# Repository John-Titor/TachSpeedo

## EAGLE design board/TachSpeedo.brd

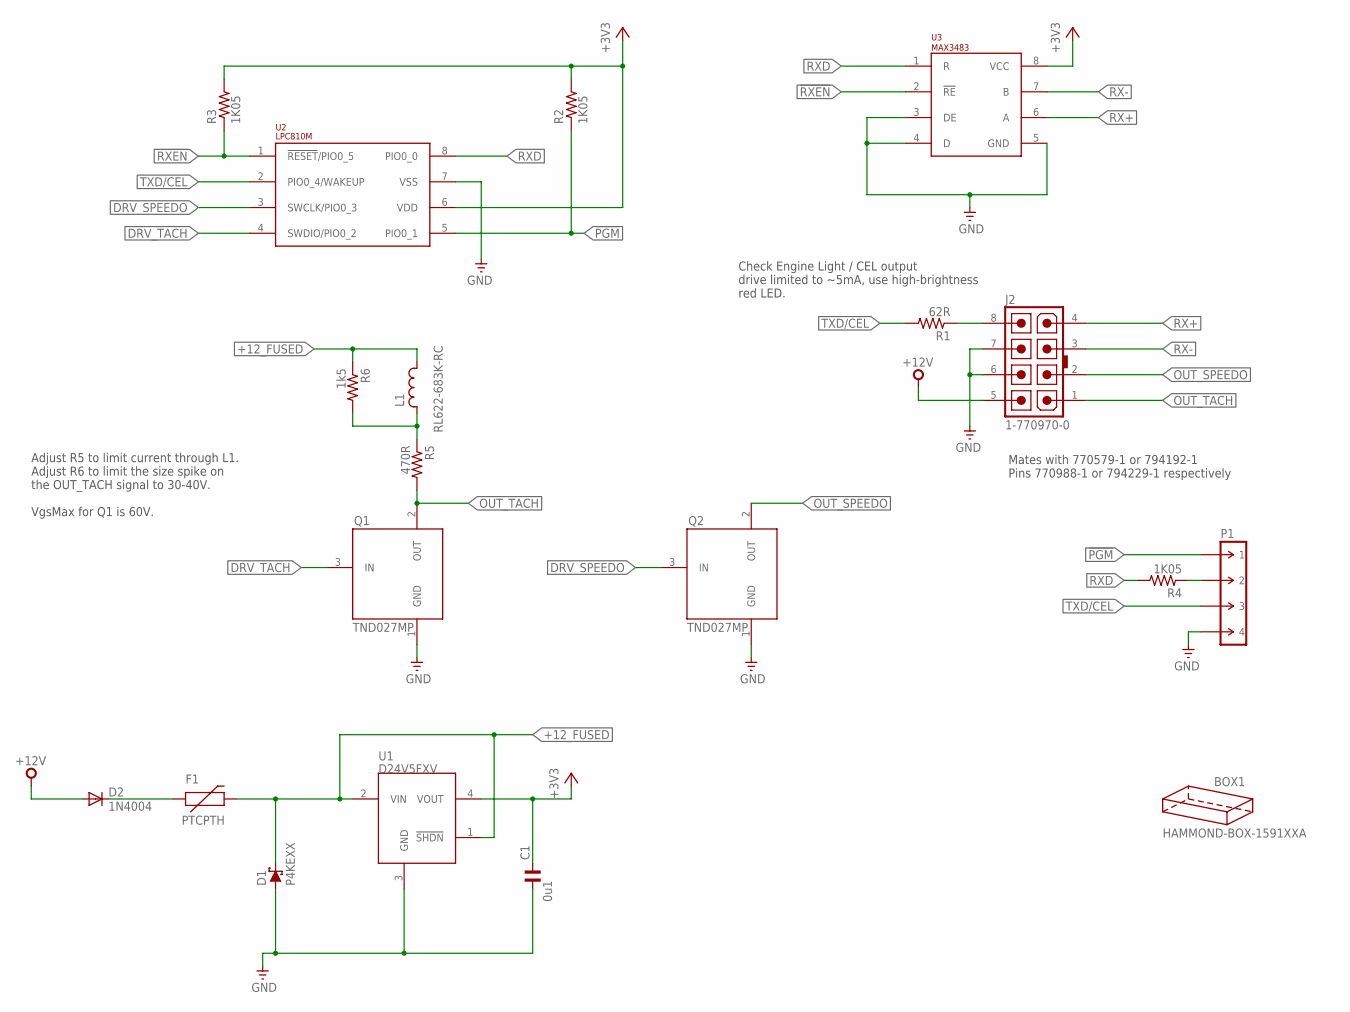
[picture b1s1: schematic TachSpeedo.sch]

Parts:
BOX1: HAMMOND-BOX-1591XXA; 1591XXA; PARTNO 1591XXAFLBK
C1: 0u1; C025-024X044; PARTNO FK18X7R1E104K
D1: P4KEXX; DO41-10; PARTNO P4KE30CA
D2: 1N4004; DO41-10; PARTNO 1N4004
F1: PTCPTH; PTC; PARTNO 600R150-RBZR
J2: 1-770970-0; PARTNO 1-770970-0
L1: RL622-683K-RC; RL622; PARTNO RL622-563K-RC
P1: M-1X04-SIP-100-40; SIP-100-04-40; PARTNO 961104-6404-AR
Q1, Q2: TND027MP; TO-92; PARTNO TND027MP-AZ
R1: 62R; 0207/10; PARTNO MFR-25FTE52-62R
R2, R3, R4: 1K05; 0207/10; PARTNO MFR-25FBF52-1K05
R5: 470R; 0207/10; PARTNO MFR-25FBF52-470R
R6: 1k5; 0207/10; PARTNO MFR-25FRF52-1K5
U1: D24V5FXV; SIP-100-04-40
U2: LPC810M; DIL08; PARTNO LPC810M021FN8FP
U3: MAX3483; DIL08; PARTNO MAX3483CPA+

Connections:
!PGM: P1.1, R2.1, U2.5 (PIO0_1)
!RXEN: R3.1, U2.1 (!RESET!/PIO0_5), U3.2 (!RE)
+3V3: C1.1, R2.2, R3.2, U1.4 (VOUT), U2.6 (VDD), U3.8 (VCC)
+12V: D2.A, J2.5
+12_FUSED: D1.C, F1.P$2 (2), L1.2, R6.1, U1.1 (!SHDN), U1.2 (VIN)
DRV_SPEEDO: Q2.3 (IN), U2.3 (SWCLK/PIO0_3)
DRV_TACH: Q1.3 (IN), U2.4 (SWDIO/PIO0_2)
GND: C1.2, D1.A, J2.6, J2.7, P1.4, Q1.1 (GND), Q2.1 (GND), U1.3 (GND), U2.7 (VSS), U3.3 (DE), U3.4 (D), U3.5 (GND)
unnamed: D2.C, F1.P$1 (1)
unnamed: P1.2, R4.1
unnamed: J2.8, R1.1
unnamed: L1.1, R5.1, R6.2
OUT_SPEEDO: J2.2, Q2.2 (OUT)
OUT_TACH: J2.1, Q1.2 (OUT), R5.2
RX+: J2.4, U3.6 (A)
RX-: J2.3, U3.7 (B)
RXD: R4.2, U2.8 (PIO0_0), U3.1 (R)
TXD/CEL: P1.3, R1.2, U2.2 (PIO0_4/WAKEUP)

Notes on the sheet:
Check Engine Light / CEL output drive limited to ~5mA, use high-brightness red LED.
Adjust R5 to limit current through L1. Adjust R6 to limit the size spike on the OUT_TACH signal to 30-40V. VgsMax for Q1 is 60V.
Mates with 770579-1 or 794192-1 Pins 770988-1 or 794229-1 respectively

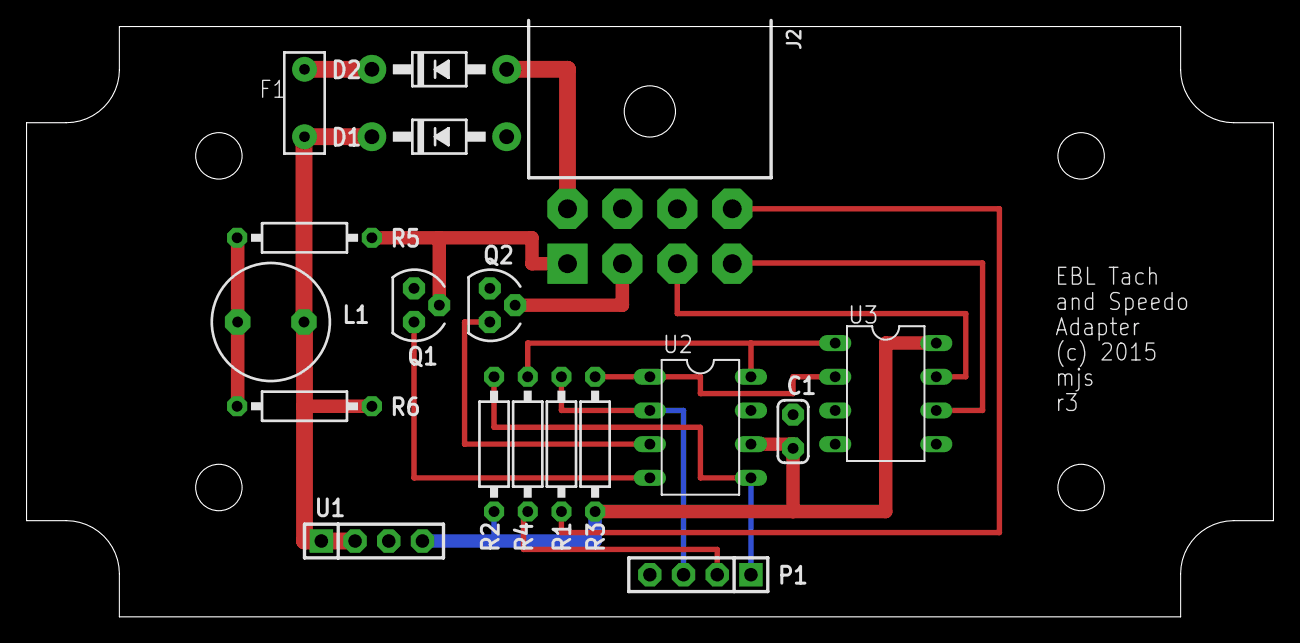
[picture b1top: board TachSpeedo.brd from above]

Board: 2 copper layers, 94.0 x 44.5 mm, 19 parts (0 on the bottom side), 18 nets.

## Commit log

2015-05-26 Initial checkin for the EBL tach/speedo adapter
2015-05-26 add ignores
2015-05-30 Handle local copy of the lpc8xx classlib
2015-05-31 EBL decoder and output controls for the r1 board
2015-06-01 Updates from testing, driving both tach and speedo now
    New speedo calculation based on experimental observation.
    Disable pulse output at zero rpm / mph
2015-06-01 Update in anticipation of the r3 board.

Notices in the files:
board/TachSpeedo.brd:
(c) 2015
